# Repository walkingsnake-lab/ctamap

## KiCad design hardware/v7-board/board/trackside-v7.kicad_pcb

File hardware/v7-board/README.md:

# Trackside V7: one custom board (a design, not built)

**V7 is a design on paper.** Nothing in this folder has been ordered, printed, assembled or tested, and no engineer has
reviewed the circuit board. The Trackside being built today is **V6** ([../bar-sleeve-case](../bar-sleeve-case/README.md)),
with bought boards inside; V6 is the pilot. V7 is what replaces V6's electronics if the pilot sells: the plan is to switch at
roughly 100 units.

## What V7 is

One circuit board in place of the three bought boards inside the case, and the changes to the case that follow from it.

| | V6 (the pilot) | V7 (this folder) |
|---|---|---|
| Controller | Adafruit Matrix Portal S3 | an ESP32-S3 module on our own board |
| Knob | Adafruit 5880 encoder board, read over I2C | the encoder soldered to the board, read directly |
| Light sensor | Adafruit VEML7700 board on a sled, under a pinhole | the VEML7700 on the board, under a thin window in the knob's collar |
| USB-C | in the end wall, plug in view | facing down inside a cable bay at the back, plug out of sight |
| Boards to wire together | three, with cables | one |
| Status | being built | drawn and quoted; not reviewed, not built |

What V7 does not change: the panel, the walnut sleeve and its slanted hood, the knob on top, what the firmware does.
The firmware's panel pins stay the same; it needs a new encoder driver (see [Firmware](#firmware-work-v7-needs)).

## How far it has got (Nov 27, 2026)

| Piece | State |
|---|---|
| Parts | Chosen. Each one checked for stock in JLCPCB's parts data. |
| Schematic | Drawn: [board/trackside-v7-schematic.pdf](board/trackside-v7-schematic.pdf). It matches the board pin for pin (47 nets). |
| Board | Placed and routed by machine on 4 layers. KiCad's design-rule check is clean. **No engineer has reviewed it.** |
| Price | Quoted at JLCPCB: $1,085.57 for 100 boards, assembled ($10.86 each). See [The quote](#the-quote). |
| Case | A 3D model with 28 fit checks, all passing. Its first pass had an independent review. Nothing printed. |
| Firmware | Not started. |

## Before anyone orders this

1. **An electrical engineer reviews the board**, and probably re-routes it by hand: the power path (the panel can draw 3 to
   4 A), the antenna's surroundings, ESD, decoupling, the USB data pair (routed here as two ordinary tracks).
2. Re-quote with the 4-layer file (the quote below was taken on an earlier 2-layer version).
3. Measure a real encoder. The case assumes its body is 6.5 mm tall; the board hangs from it.
4. Check the guide plate under the USB socket against a real plug and socket (it needs 1.05 mm; the drawings suggest 1.6).
5. Redraw the knob for the Bourns shaft (its tip sits about 1.6 mm lower than V6's knob expects).
6. Check the panel's power lead and lugs against the two M3 nuts.
7. Check part rotations in the placement file against JLCPCB's conventions, and the footprints against datasheets
   (both are JLCPCB's own, unchecked).
8. Test prints: the collar's sensor window, the board's capture in the chassis, the guide plate.
9. FCC position for a board sold under the Trackside name: not looked into.

## The board

- 92.0 x 29.5 mm, 1.2 mm thick, 4 layers: parts and signals on the two outer layers, an unbroken ground plane and an
  unbroken +5 V plane inside. A notch in the back edge and a cut-back corner fit the case.
- It hangs under the case's top wall from the knob's encoder. Most parts are on the underside. The side facing the case's
  top has only the encoder, the knob's light, the light sensor and five small parts, because there is 1.15 mm of room.
- The circuit is Adafruit's Matrix Portal S3 design (same module pins, level shifters and regulator) with these changes:
  - encoder read directly: A on GPIO 9, B on GPIO 10, switch on GPIO 11, each with a 10 k pull-up and 10 nF;
  - knob light (WS2812B-2020) on GPIO 12; status light on GPIO 4 as today, in the cable bay's ceiling;
  - VEML7700 on I2C (GPIO 16, 17), plus a 4-pin JST SH connector on the same bus that takes today's sensor board;
  - a vertical USB-C socket with ESD protection on the data lines;
  - left out: accelerometer, Up/Down buttons, analog light sensor, red LED, breakout header.
- 43 parts on 21 lines. The main ones: ESP32-S3-WROOM-1-N8R2, Bourns PEC11R-4220F-S0024 encoder, VEML7700-TT, two
  SN74AHCT245, AP2112K-3.3, a 16-pin ribbon header. LCSC numbers are in [board/bom-jlc.csv](board/bom-jlc.csv).
- Two parts are through-hole (the encoder and the ribbon header) and parts sit on both sides. Both raise the assembly price.

How it was made, plainly: the schematic and the board are generated by the scripts in `src/` from one parts table, and
the tracks were laid by an autorouter (Freerouting). That makes the files a quote needs and a sound starting point. It is
not a substitute for a person's layout.

## The case

V6's case with a new chassis. The model is [case/v7.py](case/v7.py), built on V6's (`../bar-sleeve-case/src/v6p3.py`).

- **Cable bay** at the right end, behind the panel, open to the back: the socket faces down into it, so the plug and the
  first bend of the cable are inside the case.
- **Guide plate** under the socket's mouth, with holes for the plug, the Boot and Reset buttons and the status light.
- **Sensor window:** a pocket in the translucent collar's flange leaves 0.2 mm (one printed layer) over the sensor, just
  outside the knob's edge.
- **The board is held without screws:** the encoder's nut clamps it to the collar, a keyed pocket sets its angle, and
  stops, crush ribs and a fin in the chassis take it when the chassis slides in. This is the part most likely to be
  simplified after a test print.
- The independent review of the first pass is [case/REVIEW-pass1.md](case/REVIEW-pass1.md). It found the concept sound and
  the first model impossible to assemble with real parts; those findings are fixed in the model here, and the fixes have
  not been reviewed again.

| | |
|---|---|
|  |  |

## The quote

JLCPCB, Nov 27, 2026: 100 boards, Standard assembly, both sides, taken on the earlier 2-layer version of this board.

| Line | $ |
|---|---|
| Bare boards (board 49.10, engineering 8.00, via covering 16.03, film 1.80, file check 1.05) | 75.98 |
| Components, 21 lines | 790.28 |
| Set-up 51.50, stencil 16.54 | 68.04 |
| Feeders 29.45, SMT assembly 35.22 | 64.67 |
| Manual assembly 37.95, hand-soldering 3.61, fixture 41.35 | 82.91 |
| Packaging 0.69, special components 3.00 | 3.69 |
| **Total** | **1,085.57** |

Shipping and import duty are not in it. Four layers will raise the first line. To quote again: upload
`board/trackside-v7-gerbers.zip`, set the thickness to 1.2 mm, turn on assembly (Standard, both sides), then upload
`board/bom-jlc.csv` and `board/cpl-jlc.csv`.

## Firmware work V7 needs

- Read the encoder on GPIO 9 (A), 10 (B), 11 (switch). The Bourns part gives 24 pulses and 24 detents per turn.
- Drive the knob's light directly on GPIO 12.
- Ignore the light sensor while the knob's light is on (the light reaches it).
- Retune the dark and bright levels: the sensor sees more light than under V6's pinhole.
- Unchanged: the HUB75 pin map, the TinyUF2 loader and double-tap reset, flashing over USB, I2C on GPIO 16/17.

## What is in this folder

| Path | What |
|---|---|
| `board/trackside-v7.kicad_pro` | The KiCad 7 project: schematic and board. Open this. |
| `board/trackside-v7-schematic.pdf`, `schematic.png` | The schematic, to read without KiCad. |
| `board/trackside-v7-gerbers.zip`, `bom-jlc.csv`, `cpl-jlc.csv` | The three files a JLCPCB quote takes. |
| `board/netlist.csv`, `placement.txt`, `drc.txt` | Every net and its pins; where each part sits in the case; KiCad's check report. |
| `board/jlc.pretty/`, `jlc.kicad_sym` | Footprints and symbols (JLCPCB's own, fetched through EasyEDA). The 3D models are not kept (39 MB); `easyeda2kicad` fetches them by LCSC number into `board/jlc.3dshapes/`. |
| `src/` | The scripts that make all of the above. |
| `case/` | The case model, its renders and the review of its first pass. |

## Making it again

Needs KiCad 7 (its `pcbnew` Python module and `kicad-cli`), Java, `xvfb-run`, and Freerouting 1.9.0 saved as
`src/tools/fr-1.9.0.jar` (not kept in the repo).

```
cd src
python3 build_all.py     # places the parts, routes, checks, exports. Repeats the router until nothing is unconnected.
python3 gen_sch.py       # draws the schematic from the same parts table
python3 check_sch.py     # compares the schematic's netlist with the board's
cd ../case
python3 v7.py            # the case model's 28 fit checks ("render" as an argument draws the pictures)
```

`gen_board.py` on its own writes an unrouted board over the routed one. The router's result differs from run to run, so a
rebuilt board will not match this one track for track. KiCad's check reports no violations with two library-bookkeeping
checks switched off in the project: the footprints were edited on the board (silkscreen trimmed off pads, part names
moved), so they no longer match their library copies.

## Licence

The circuit is derived from the Adafruit Matrix Portal S3 by Limor Fried/Ladyada for Adafruit Industries, published under
Creative Commons Attribution/Share-Alike. A board made from these files must credit Adafruit and be shared under the same
terms. The credit is on the board's silkscreen and in the schematic's title block.

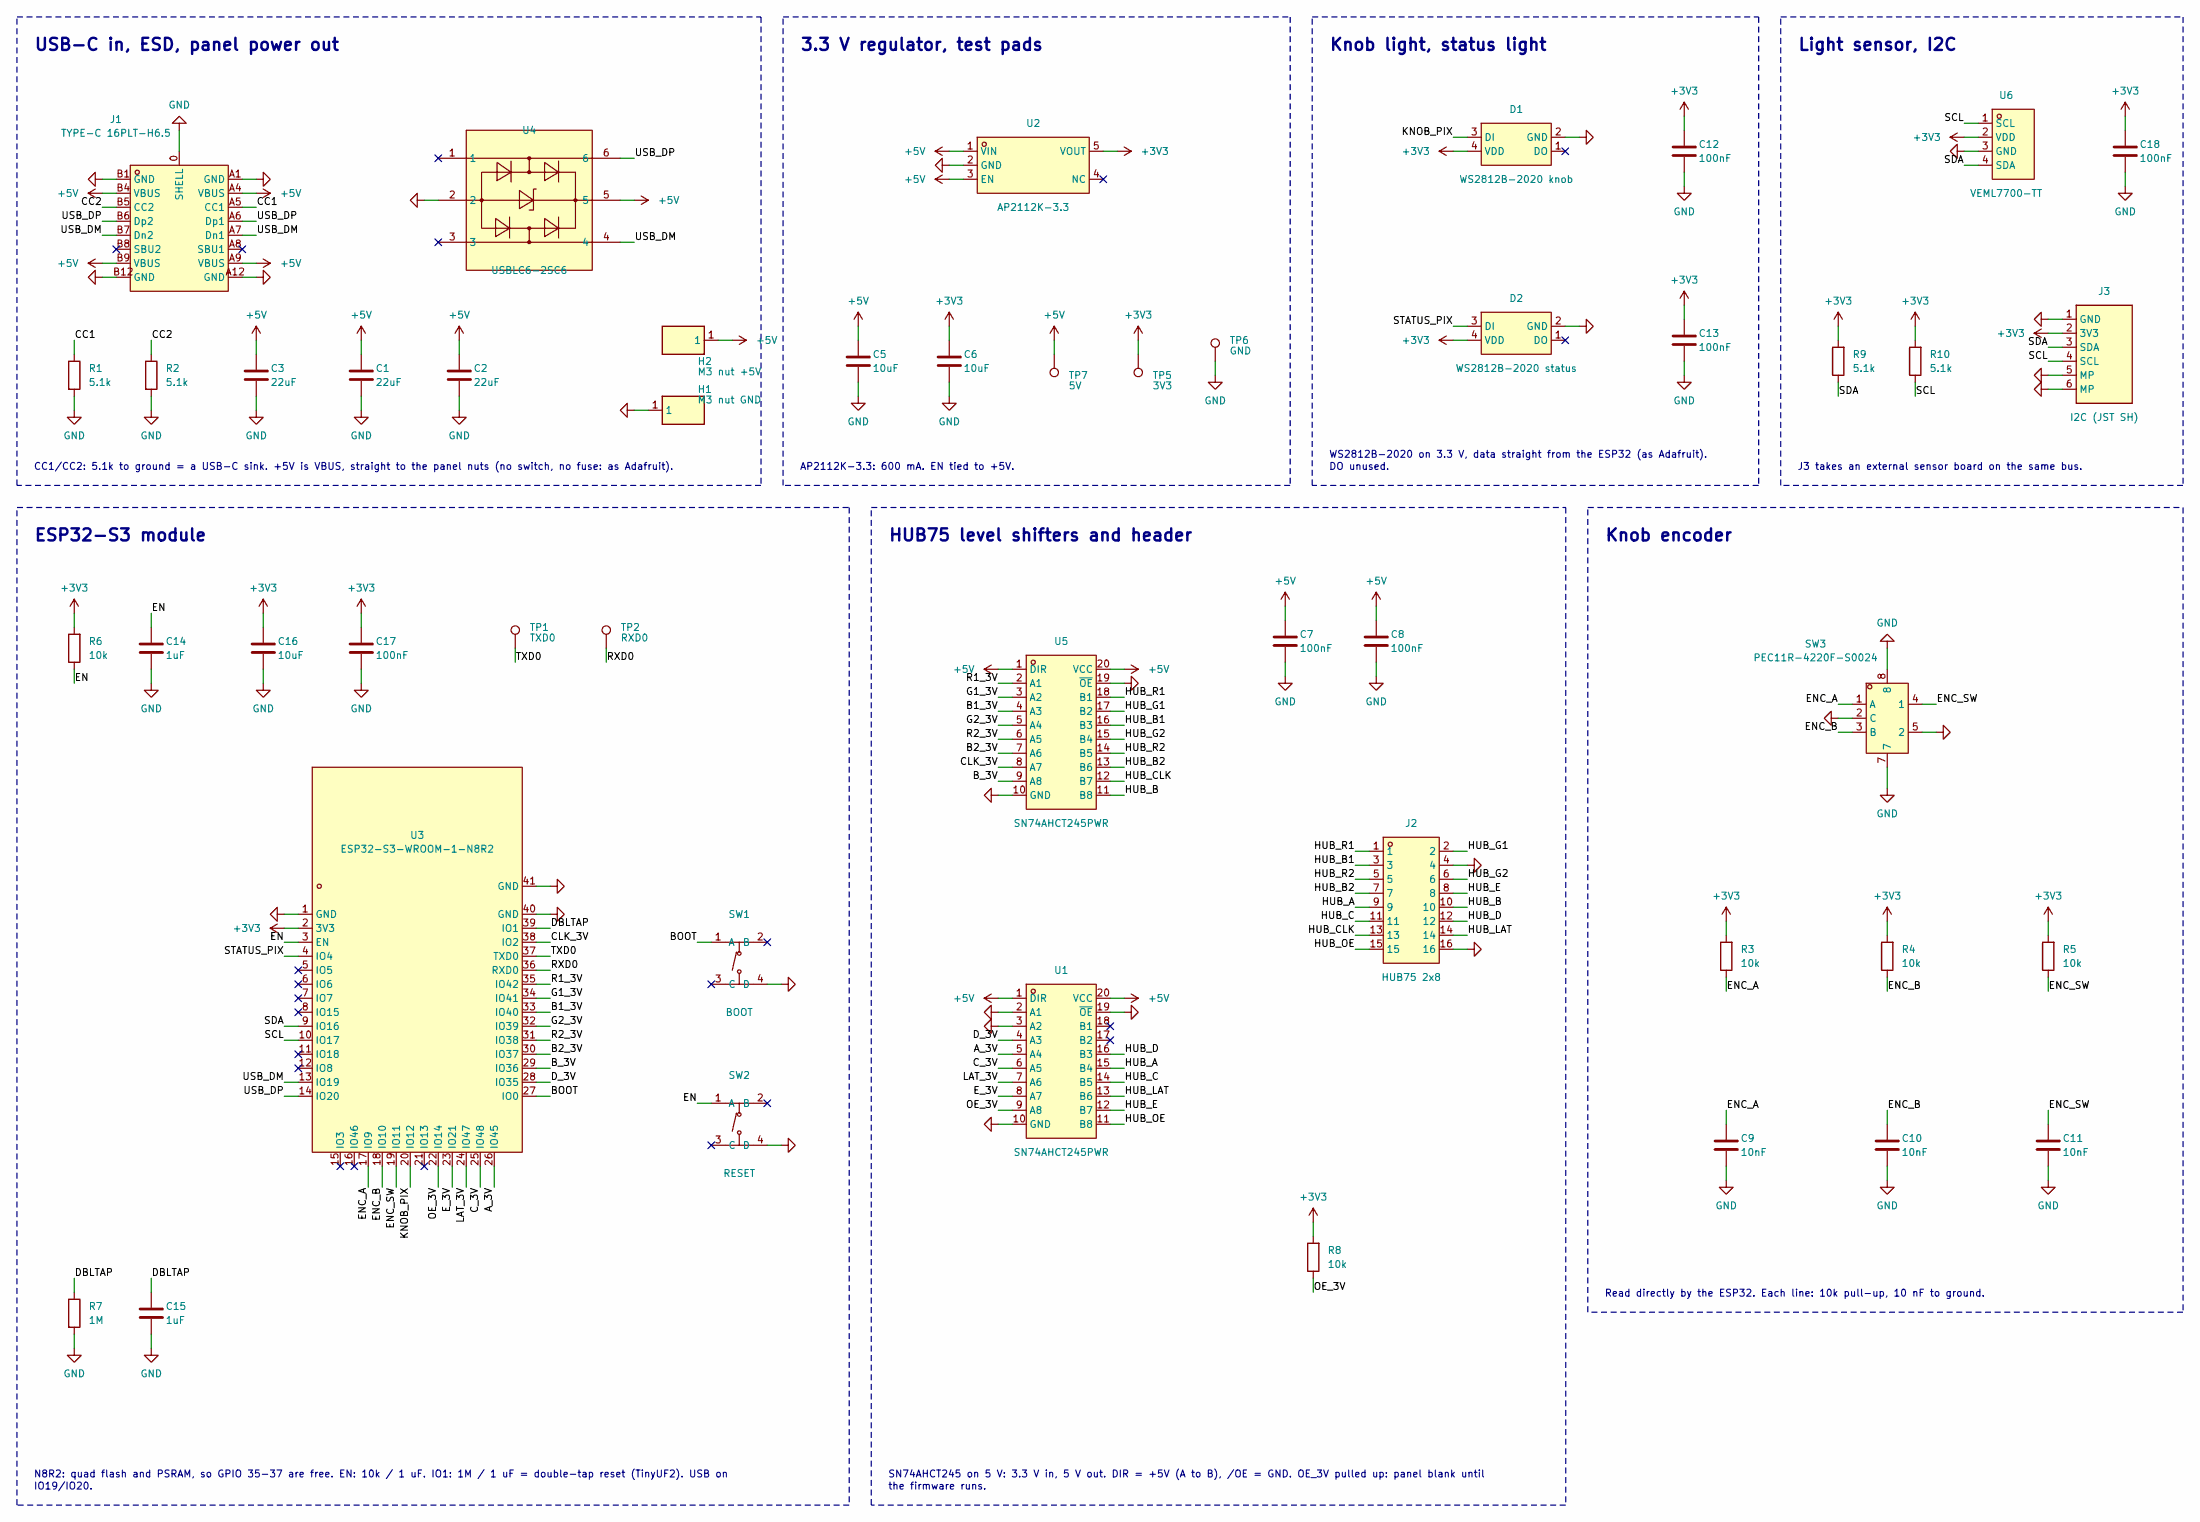
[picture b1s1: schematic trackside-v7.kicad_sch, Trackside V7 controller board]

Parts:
C1, C2, C3: 22uF; C0805; LCSC C45783
C5, C6: 10uF; C0805; LCSC C15850
C7, C8, C12, C13, C17, C18: 100nF; C0603; LCSC C14663
C9, C10, C11: 10nF; C0603; LCSC C57112
C14, C15: 1uF; C0603; LCSC C15849
C16: 10uF; C0603; LCSC C19702
D1: WS2812B-2020 knob; LED-SMD_4P-L2.2-W2.0-P1.00_WS2815C-2020-4P; LCSC C52917434
D2: WS2812B-2020 status; LED-SMD_4P-L2.2-W2.0-P1.00_WS2815C-2020-4P; LCSC C52917434
H1: M3 nut GND; SMD_BD5.6-D4.1; LCSC C2915308
H2: M3 nut +5V; SMD_BD5.6-D4.1; LCSC C2915308
J1: TYPE-C 16PLT-H6.5; USB-C-SMD_SOUHAN_TYPE-C-16PLT-H6.5; LCSC C3151748
J2: HUB75 2x8; IDC-TH_16P-P2.54_C3406; LCSC C2977594
J3: I2C (JST SH); CONN-SMD_4P-P1.00_SM04B-SRSS-TB-LF-SN; LCSC C160404
R1, R2, R9, R10: 5.1k; R0603; LCSC C23186
R3, R4, R5, R6, R8: 10k; R0603; LCSC C25804
R7: 1M; R0603; LCSC C22935
SW1: BOOT; SW-SMD_4P-L5.1-W5.1-P3.70-LS6.5-TL_H1.5; LCSC C318884
SW2: RESET; SW-SMD_4P-L5.1-W5.1-P3.70-LS6.5-TL_H1.5; LCSC C318884
SW3: PEC11R-4220F-S0024; SW-TH_5P-L12.5-W13.4-P2.50-LS14.5-EH13.2; LCSC C143797
TP1: TXD0; TestPoint_Pad_D1.5mm
TP2: RXD0; TestPoint_Pad_D1.5mm
TP5: 3V3; TestPoint_Pad_D1.5mm
TP6: GND; TestPoint_Pad_D1.5mm
TP7: 5V; TestPoint_Pad_D1.5mm
U1, U5: SN74AHCT245PWR; TSSOP-20_L6.5-W4.4-P0.65-LS6.4-BL; LCSC C10910
U2: AP2112K-3.3; SOT-25-5_L2.9-W1.6-P0.95-LS2.8-BL; LCSC C51118
U3: ESP32-S3-WROOM-1-N8R2; WIRELM-SMD_ESP32-S3-WROOM-1; LCSC C2913204
U4: USBLC6-2SC6; SOT-23-6_L2.9-W1.6-P0.95-LS2.8-BL; LCSC C7519
U6: VEML7700-TT; SENSOR-SMD_EML7700-TT; LCSC C1850416

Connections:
+3V3: C6.1, C12.1, C13.1, C16.1, C17.1, C18.1, D1.4 (VDD), D2.4 (VDD), J3.2 (3V3), R3.2, R4.2, R5.2, R6.2, R8.2, R9.2, R10.2, TP5.1, U2.5 (VOUT), U3.2 (3V3), U6.2 (VDD)
+5V: C1.1, C2.1, C3.1, C5.1, C7.1, C8.1, H2.1, J1.A4 (VBUS), J1.A9 (VBUS), J1.B4 (VBUS), J1.B9 (VBUS), TP7.1, U1.1 (DIR), U1.20 (VCC), U2.1 (VIN), U2.3 (EN), U4.5, U5.1 (DIR), U5.20 (VCC)
A_3V: U1.5 (A4), U3.26 (IO45)
B1_3V: U3.33 (IO40), U5.4 (A3)
B2_3V: U3.30 (IO37), U5.7 (A6)
BOOT: SW1.1 (A), U3.27 (IO0)
B_3V: U3.29 (IO36), U5.9 (A8)
CC1: J1.A5 (CC1), R1.1
CC2: J1.B5 (CC2), R2.1
CLK_3V: U3.38 (IO2), U5.8 (A7)
C_3V: U1.6 (A5), U3.25 (IO48)
DBLTAP: C15.1, R7.1, U3.39 (IO1)
D_3V: U1.4 (A3), U3.28 (IO35)
EN: C14.1, R6.1, SW2.1 (A), U3.3 (EN)
ENC_A: C9.1, R3.1, SW3.1 (A), U3.17 (IO9)
ENC_B: C10.1, R4.1, SW3.3 (B), U3.18 (IO10)
ENC_SW: C11.1, R5.1, SW3.4 (1), U3.19 (IO11)
E_3V: U1.8 (A7), U3.23 (IO21)
G1_3V: U3.34 (IO41), U5.3 (A2)
G2_3V: U3.32 (IO39), U5.5 (A4)
GND: C1.2, C2.2, C3.2, C5.2, C6.2, C7.2, C8.2, C9.2, C10.2, C11.2, C12.2, C13.2, C14.2, C15.2, C16.2, C17.2, C18.2, D1.2 (GND), D2.2 (GND), H1.1, J1.0 (SHELL), J1.A1 (GND), J1.A12 (GND), J1.B1 (GND), J1.B12 (GND), J2.4, J2.16, J3.1 (GND), J3.5 (MP), J3.6 (MP), R1.2, R2.2, R7.2, SW1.4 (D), SW2.4 (D), SW3.2 (C), SW3.5 (2), SW3.7, SW3.8, TP6.1, U1.2 (A1), U1.3 (A2), U1.10 (GND), U1.19 (~OE), U2.2 (GND), U3.1 (GND), U3.40 (GND), U3.41 (GND), U4.2, U5.10 (GND), U5.19 (~OE), U6.3 (GND)
HUB_A: J2.9, U1.15 (B4)
HUB_B: J2.10, U5.11 (B8)
HUB_B1: J2.3, U5.16 (B3)
HUB_B2: J2.7, U5.13 (B6)
HUB_C: J2.11, U1.14 (B5)
HUB_CLK: J2.13, U5.12 (B7)
HUB_D: J2.12, U1.16 (B3)
HUB_E: J2.8, U1.12 (B7)
HUB_G1: J2.2, U5.17 (B2)
HUB_G2: J2.6, U5.15 (B4)
HUB_LAT: J2.14, U1.13 (B6)
HUB_OE: J2.15, U1.11 (B8)
HUB_R1: J2.1, U5.18 (B1)
HUB_R2: J2.5, U5.14 (B5)
KNOB_PIX: D1.3 (DI), U3.20 (IO12)
LAT_3V: U1.7 (A6), U3.24 (IO47)
OE_3V: R8.1, U1.9 (A8), U3.22 (IO14)
R1_3V: U3.35 (IO42), U5.2 (A1)
R2_3V: U3.31 (IO38), U5.6 (A5)
RXD0: TP2.1, U3.36 (RXD0)
SCL: J3.4 (SCL), R10.1, U3.10 (IO17), U6.1 (SCL)
SDA: J3.3 (SDA), R9.1, U3.9 (IO16), U6.4 (SDA)
STATUS_PIX: D2.3 (DI), U3.4 (IO4)
TXD0: TP1.1, U3.37 (TXD0)
USB_DM: J1.A7 (Dn1), J1.B7 (Dn2), U3.13 (IO19), U4.4
USB_DP: J1.A6 (Dp1), J1.B6 (Dp2), U3.14 (IO20), U4.6

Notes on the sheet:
USB-C in, ESD, panel power out
CC1/CC2: 5.1k to ground = a USB-C sink. +5V is VBUS, straight to the panel nuts (no switch, no fuse: as Adafruit).
3.3 V regulator, test pads
AP2112K-3.3: 600 mA. EN tied to +5V.
Knob light, status light
WS2812B-2020 on 3.3 V, data straight from the ESP32 (as Adafruit).
DO unused.
Light sensor, I2C
J3 takes an external sensor board on the same bus.
ESP32-S3 module
N8R2: quad flash and PSRAM, so GPIO 35-37 are free. EN: 10k / 1 uF. IO1: 1M / 1 uF = double-tap reset (TinyUF2). USB on
IO19/IO20.
HUB75 level shifters and header
SN74AHCT245 on 5 V: 3.3 V in, 5 V out. DIR = +5V (A to B), /OE = GND. OE_3V pulled up: panel blank until
the firmware runs.
Knob encoder
Read directly by the ESP32. Each line: 10k pull-up, 10 nF to ground.

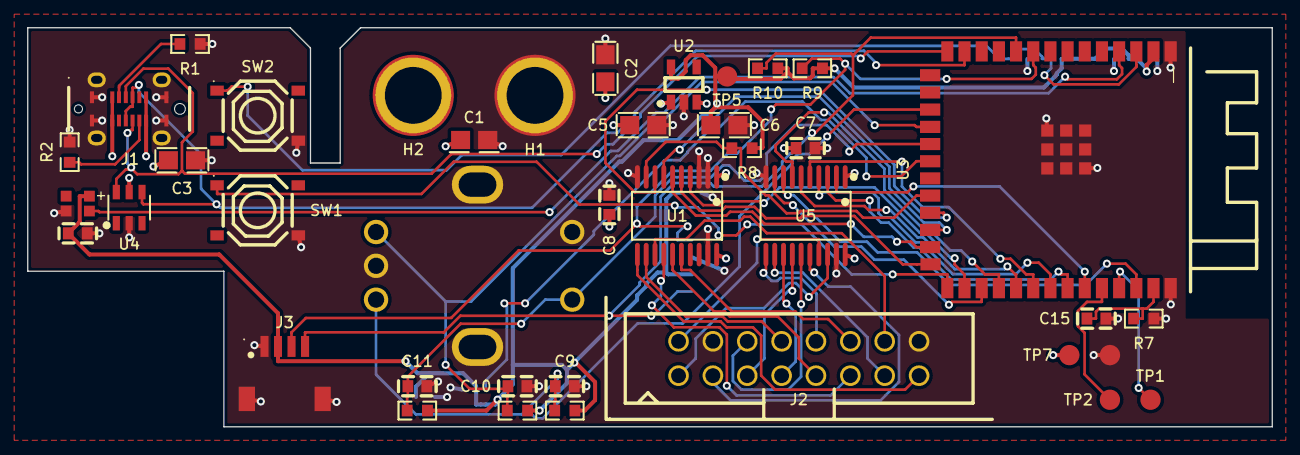
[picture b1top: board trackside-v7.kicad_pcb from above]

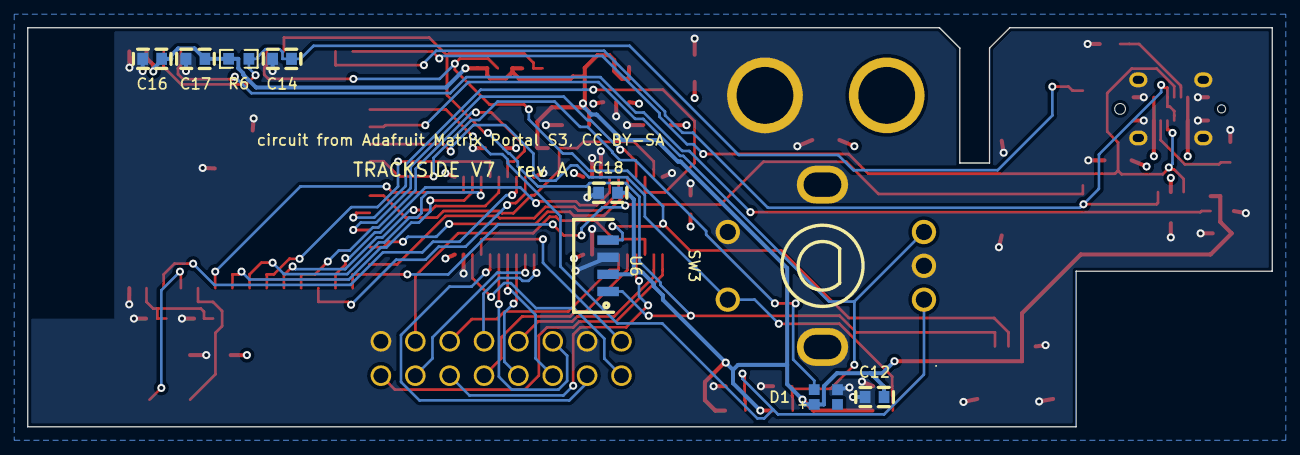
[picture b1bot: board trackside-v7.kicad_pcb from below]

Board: 4 copper layers, 92.0 x 29.5 mm, 48 parts (9 on the bottom side), 47 nets.

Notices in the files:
hardware/v7-board/board/trackside-v7.kicad_pcb:
circuit from Adafruit Matrix Portal S3, CC BY-SA
hardware/v7-board/board/trackside-v7.kicad_sch:
Circuit derived from the Adafruit Matrix Portal S3 (Limor Fried/Ladyada, CC BY-SA).
